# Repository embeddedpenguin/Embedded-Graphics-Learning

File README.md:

# Embedded-Graphics-Learning

This repository is old and outdated. Please visit https://git.epenguin.net/penguin/Embedded-Graphics for the updated repo.

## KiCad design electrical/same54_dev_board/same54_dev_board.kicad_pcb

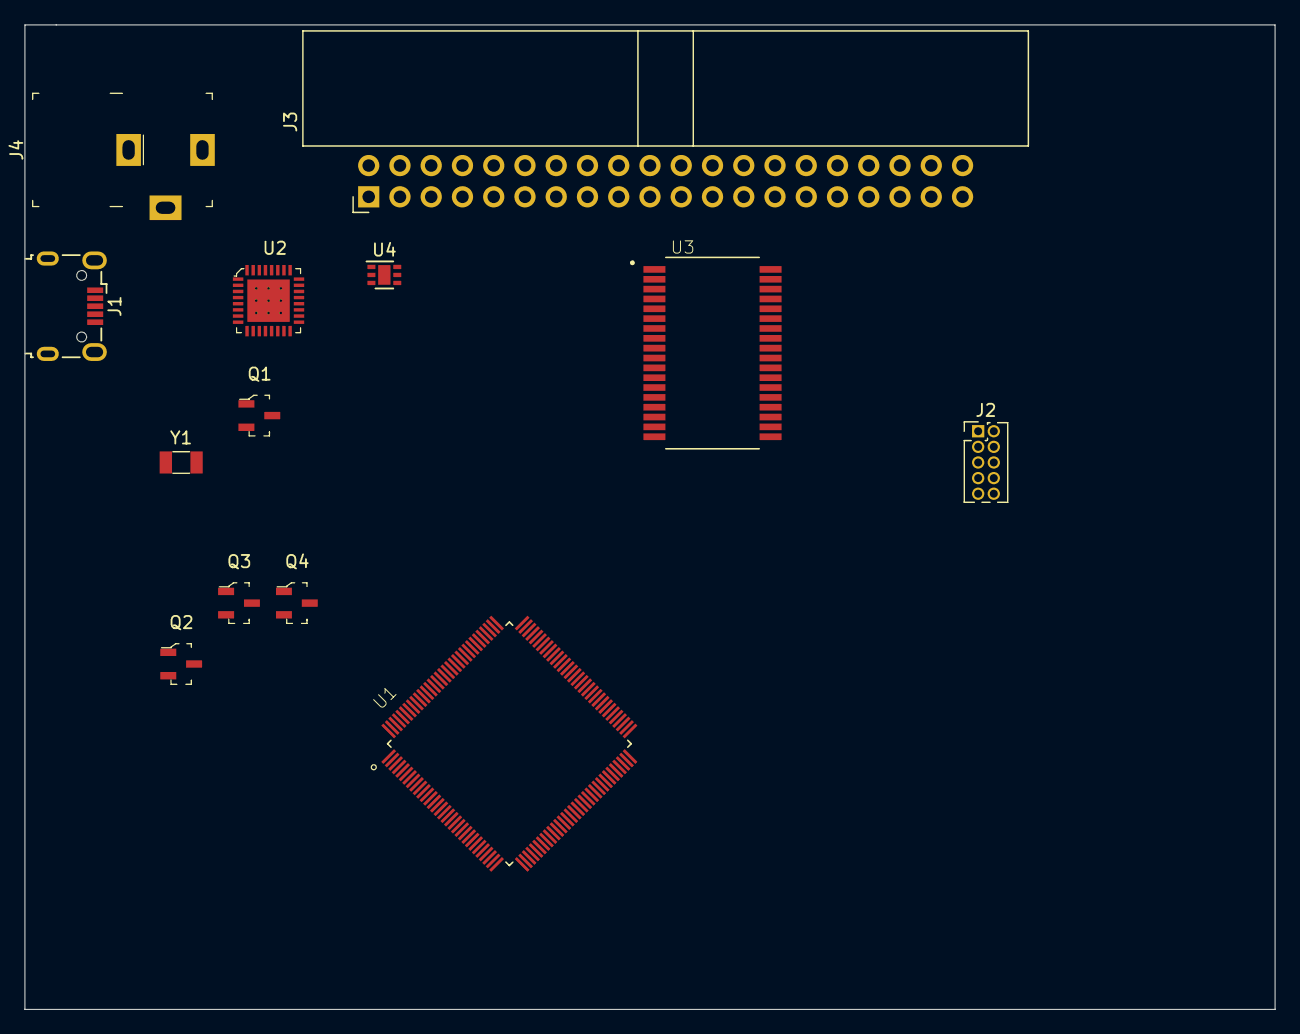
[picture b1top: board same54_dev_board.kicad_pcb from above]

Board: 2 copper layers, 101.6 x 80.0 mm, 13 parts (0 on the bottom side), 44 nets, no tracks yet.

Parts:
J1: USB_B_Micro; USB_Micro-B_Wuerth_629105150521
J2: Conn_ARM_JTAG_SWD_10; PinHeader_2x05_P1.27mm_Vertical
J3: Conn_02x20_Odd_Even_LCD_INTF; IDC-Header_2x20_P2.54mm_Horizontal
J4: Barrel_Jack_Switch; Barrel_Jack_5.5mmODx2.1mmID_PJ-102A
Q1: Default PFET_A; SOT-23-3
Q2: Alt PFET_A; SOT-23-3
Q3: Default PFET_B; SOT-23-3
Q4: Alt PFET_B; SOT-23-3
U1: p_ATSAME54P20A-AU; QFP40P1600X1600X120-128N_ATSAME54P20A
U2: FT232RQ-REEL; QFN-32-1EP_5x5mm
U3: MAX7301AAX+; SOP80P1030X264-36N
U4: NCP349MNAETBG; DFN-6-1EP_2x2mm_P0.65mm_EP1x1.6mm
Y1: XOSC32; Crystal_SMD_3215-2Pin_3.2x1.5mm

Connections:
/DEBUG_RX: U1.100, U2.30
/DEBUG_TX: U1.101, U2.2
/MASTER_I2C_SCL: J3.3, U1.67
/MASTER_I2C_SDA: J3.4, U1.66
/MASTER_SPI_CLK: U1.22, U3.33
/MASTER_SPI_MISO: U1.21, U1.23, U3.4
/s_Power/USB_3v3: Q1.1, Q2.2, Q3.1
/s_SCREEN_INTF/D0: J3.13, U3.5
/s_SCREEN_INTF/D1: J3.14, U3.6
/s_SCREEN_INTF/D2: J3.15, U3.7
/s_SCREEN_INTF/D3: J3.16, U3.8
/s_SCREEN_INTF/D4: J3.17, U3.9
/s_SCREEN_INTF/D5: J3.18, U3.10
/s_SCREEN_INTF/D6: J3.19, U3.11
/s_SCREEN_INTF/D7: J3.20, U3.12
/s_SCREEN_INTF/D8: J3.21, U3.13
/s_SCREEN_INTF/D9: J3.22, U3.14
/s_SCREEN_INTF/D10: J3.23, U3.15
/s_SCREEN_INTF/D11: J3.24, U3.16
/s_SCREEN_INTF/D12: J3.25, U3.17
/s_SCREEN_INTF/D13: J3.26, U3.18
/s_SCREEN_INTF/D14: J3.27, U3.19
/s_SCREEN_INTF/D15: J3.28, U3.20
/s_SCREEN_INTF/D16: J3.29, U3.21
/s_SCREEN_INTF/D17: J3.30, U3.22
/s_SCREEN_INTF/D18: J3.31, U3.23
/s_SCREEN_INTF/D19: J3.32, U3.24
/s_SCREEN_INTF/D20: J3.33, U3.25
/s_SCREEN_INTF/D21: J3.34, U3.26
/s_SCREEN_INTF/D22: J3.35, U3.27
/s_SCREEN_INTF/D23: J3.36, U3.28
/s_USB_INTF.sch/FTDI_3V3: U2.1, U2.9, U2.16
/s_USB_INTF.sch/USB_D+: J1.3, U2.14
/s_USB_INTF.sch/USB_D-: J1.2, U2.15
GND: J1.5, J1.6, J2.3, J2.5, J2.9, J3.2, J4.2, U2.4, U2.17, U2.20, U2.24, U2.26, U2.33, U3.2, U3.3, U4.2, U4.4
unnamed: U1.1, Y1.2
unnamed: U1.2, Y1.1
unnamed: Q3.2, Q4.2, U4.1
unnamed: Q1.3, Q2.1, Q3.3, Q4.1
unnamed: Q2.3, Q4.3
unnamed: U1.14, U1.25
unnamed: U1.46, U1.54, U1.65, U1.79, U1.91, U1.97, U1.107, U1.118
unnamed: U4.5, U4.6
g_3v3: J3.1, U1.128, U3.36

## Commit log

2020-03-15 finished making e54 symbol... snapeda one was garbage
2020-03-17 finished same54 symbol, added some more symbols, created 2x20 connector for lcd
2020-03-17 added .gitignore
2020-03-19 made some connections, creating firmware base from asf4
2020-03-20 more connections, need to update readmes with proper docs
2020-03-20 Added hierarchical pins for some components, finished io expander to lcd bus, going with 2x20 icd block header for the tft bus but dont have a part number for digikey
2020-03-24 Trying to figure out how I want to do power...
2020-03-24 going with barrel jack 5v+2A optional input, with usb supplying 400mA + 100mA for internals
2020-03-24 Added usart, i2c, and spi pin locations, as well as labeled sercoms
2020-03-24 Made board smaller, changed some small things
2020-04-19 migrating to laptop
2020-04-19 added testing sw for xplained
2020-04-20 restructuring test sw project
2020-05-02 added new testing proj
2020-05-05 started on framework for test projecgt
2020-05-20 testing
2020-05-22 preparing a fix
2020-05-22 added lvgl
2020-05-22 added hw pin mappings for ssd1963
2020-05-22 stuck on these stupid lcd driver variables again
2020-05-23 prepping d21 test project
2020-05-23 d21 somewhat stable now, still no screen output rip
2020-05-23 fixed usart callbacks not working
2020-05-24 Got the screen to power on using the D21! There was an electrical issue... It will be documented -_-
2020-05-25 added idc header breakout board to replace the rpi one that gave me trouble
2020-05-25 d21 now has a working image!
2020-05-26 remade the e54 project because the first one shit the bed zzz
2020-05-27 e54 working with the screen for the first time ever! it is still buggy but huge milestone
2020-05-28 SAME54 consistently presenting a nice image!
2020-05-28 moving away from atmel studio. its become too much of a burden to keep using
2020-05-31 almost got makefile working!
2020-05-31 custom makefile working!
